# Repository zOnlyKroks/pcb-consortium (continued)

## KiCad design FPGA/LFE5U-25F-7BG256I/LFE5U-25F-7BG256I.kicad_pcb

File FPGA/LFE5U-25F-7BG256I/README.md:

# ECP5 emulation board (LFE5U-25F, caBGA-256)

FPGA board for emulating our custom MCUs and soft cores. Schematic done; PCB placed, fanned out and routed (DRC: 0 unconnected, 0 clearance errors).

## What's on it

| Block | Part | Notes |
|---|---|---|
| FPGA | LFE5U-25F-6BG256C (C1521614) | 24k LUT, 56 DSP, 1 Mbit BRAM. Same footprint and pinout as the -7BG256I placed in the symbol. All banks run at 3.3 V. |
| Config | W25Q32JVSSIQ, 4 MB QSPI | Master SPI boot (CFG = 010). The rest of the flash is free for user data. Buttons for PROGRAMN and a DONE LED. |
| USB | USB-C + CH347F | JTAG to the ECP5 (`openFPGALoader -c ch347`). UART0 + SPI go to bank 7 for the emulated core. Board power comes from USB (1.1 A PTC). |
| RAM | W9812G6KH-6, 16 MB SDR, x16 | 166 MHz. The footprint also fits the 32 MB W9825G6KH; route spare ball M15 to pin 36 (A12) for that. |
| Clock | 25 MHz oscillator on P6 | P6 is the PLL input LLC_GPLL0T_IN. |
| Video | 12-bit VGA (4-4-4 resistor DAC) + HDMI connector | HDMI carries DVI as LVCMOS33D pairs, plus DDC and HPD. |
| Audio | 3.5 mm line out | PWM / sigma-delta through an RC filter. |
| User I/O | 8 LEDs, 8 DIP switches, 4 buttons, 4-digit 7-segment, microSD | |
| Expansion | 4x PMOD (A/B on bank 0, C/D on bank 2) | Also a 40-pin header with 34 GPIO, +5 V, +3.3 V and GND. |
| Power | 2x SY8089 buck (3.3 V, 1.1 V), AP2112K-2.5 LDO (VCCAUX) | |

## Files

- `LFE5U-25F-7BG256I.kicad_sch` is the root sheet. It holds the FPGA units as placed in KiCad, moved right by 63.5 mm so they sit inside the A3 frame. The sub-sheets are power, config, usb_jtag, sdram, video_audio and user_io.
- `constraints/LFE5U-25F-7BG256I.lpf` holds the pin constraints for nextpnr-ecp5 / Diamond: 180 ports, with PULLMODE set for the switches, buttons and SD. Build with `nextpnr-ecp5 --25k --package CABGA256 --speed 6`.
- `tools/design.py` assigns every ball to a net. It is the single source for the schematic labels, the LPF and the netlist check.
- `tools/gen_sch.py` generates every sheet. Re-run it after editing `design.py`. Before re-running, diff `.history` for edits made in KiCad.
- `tools/check_netlist.py` exports the netlist and checks it against `design.py` plus the local nets. It still expects the old references J503/J601 for the audio jack and microSD, which are now CN1/Card1.
- `tools/place_pcb.py` places the PCB, then `tools/fanout_pcb.py` does the BGA and plane fan-out.
- `tools/route_prep.py`, `route_finish.py`, `route_cleanup.py` and `route_leftovers.py` do the routing (see Routing below).
- `tools/build_lib.py` builds `libs/fpga_board.kicad_sym` (SY8089, CH347F).

## PCB

The board is 100 x 100 mm, 6 layers, 1.6 mm thick:

| Layer | Use |
|---|---|
| F.Cu | signals |
| In1 | GND |
| In2 | signals |
| In3 | signals |
| In4 | +3V3, with a +1V1 island under the BGA |
| B.Cu | signals |

It started out as 4 layers. Freerouting stalled there at about 60 unrouted connections on two signal layers, so the board went to 6 layers. The stackup in the board file is JLC's 1.6 mm 6-layer build: 2313 prepreg on the outsides, 0.565 mm cores, and 2116 prepreg in the middle. The values are nominal, because the board is ordered without impedance control. In2 and In3 sit only about 0.13 mm apart, so long parallel runs between them should be avoided.

All parts are on the top side. `tools/place_pcb.py` does the placement: it only moves footprints and sets up the layers, rules and net classes. `tools/fanout_pcb.py` then does the BGA and plane fan-out, and the routing tools do the rest (see below). The edges follow the FPGA banks:

| Edge | What's there | Bank |
|---|---|---|
| Top | PMOD A, PMOD B | 0 |
| Top | HDMI, VGA | 1 |
| Right | microSD, audio, PMOD C/D, with the SDRAM just inside | 2 / 3 |
| Left | USB-C, GPIO header, with power and the CH347 next to the USB | 7 / 6 |
| Bottom | 7-segment, LEDs, DIP switches, buttons; flash and config sit under the BGA | 6 / 8 |

The middle of each BGA side is kept free for fan-out, and the FPGA decoupling sits in the four corners.

### Fan-out

`tools/fanout_pcb.py` escapes all 197 used balls. Each escape ends 1.6 mm outside the outer ball row, so routing starts outside the BGA.

| Balls | Escape |
|---|---|
| Ring 0 (outer row) | F.Cu, straight out |
| Ring 1 | F.Cu, through the channel between two ring-0 balls |
| Ring 2, where a ring-0 channel is still free (8 balls) | F.Cu, straight out, no via |
| Remaining rings 2-5 (94 balls) | Dog-bone via, then a 0.1 mm B.Cu track. A small maze router picks each via's interstitial together with its path. |
| GND, +3V3, +1V1 | Dog-bone via to the plane. F7 and H7 (+3V3 deep in the core) link to their neighbour on F.Cu. |

Why the maze router: straight lanes jam. The ring-2 vias form a wall that passes one track per gap, and between two walls there is room for only one sideways track.

The In4 +1V1 island is shaped around the core. It covers the core square, then runs up an arm through the middle of the top side (no vias in that interstitial column), then along a bar above the BGA. The bar carries all six 100 nF +1V1 caps and C220 from the regulator. For that, C224/C225 swapped places with C242/C243.

The inner planes use 0.1 mm clearance and 0.1 mm minimum width, so copper still flows between two vias 0.8 mm apart. Without that, the 3.3 V plane and the 1.1 V island broke into pieces.

Every other GND/+3V3/+1V1 SMD pad gets a stub and via into its plane where one fits. All fan-out copper is locked, so Freerouting keeps it. Nine plane pads had no room for a via (the regulator side of +1V1, the J502 GND pins, U301 pin 6). Routing ties them to the nearest via of their net. Re-running the script strips the fan-out and redoes it. It refuses to run once there are unlocked (routed) tracks.

Vias must stay out of the In4 arm above the BGA (x 42.4-45.6 mm, y 27-32 mm from the board corner). It is the only feed into the 1.1 V core. A no-via rule area named "+1V1 arm" enforces this, both in DRC and in the Freerouting DSN.

### Routing

1. `tools/route_prep.py` writes `route/LFE5U-25F-7BG256I.dsn`. It takes the plane nets out of the job: Freerouting doesn't treat inner planes as connections, so their fixed copper becomes a netless obstacle. The nine via-less plane pads are routed as small `<net>__<n>` nets to the nearest via of their net. The router's via types are named from the layer count (`Via[0-5]_...` on 6 layers). Earlier the 4-layer names were left in, and Freerouting then could hardly place any vias.
2. Freerouting 2.4.1 from the KiCad plugin, headless:
   `java -Djava.awt.headless=true -jar freerouting-2.4.1.jar -de LFE5U-25F-7BG256I.dsn -do LFE5U-25F-7BG256I.ses -mp 100 -mt 8 --gui.enabled=false --router.job_timeout="01:30:00"`
   It stopped on its own after 28 passes (20 min) with 8 connections open. `route/watch.ps1` shows its progress.
3. `tools/route_finish.py` imports the session, and `tools/route_cleanup.py` strips the copper that leads nowhere. With In2/In3 free, Freerouting mostly left each BGA via on an inner layer, so most 0.1 mm B.Cu escapes ended up as dead ends. Cleanup uses KiCad's DRC to decide what dangles. It trims a track back to a junction rather than deleting it, and it undoes any round that would open a connection.
4. `tools/route_leftovers.py` routes what is still open. It is a 0.05 mm grid router on the four signal layers with rip-up and reroute: other nets' unlocked routing is a soft obstacle, and whatever it crosses gets rerouted. Fan-out, pads and plane copper are hard obstacles. Afterwards it bridges near misses that the grid saw as joined. It routed the last 6 (the HDMI pairs, HDMI_SCL, CH_RXD, GPIO32, PMODD6) after moving a few HDMI/VGA/PMOD-B neighbours.

What DRC still reports is cosmetic: 10 dead-end stubs of 0.02-0.5 mm and 5 vias that join two tracks on one layer, all around the top edge of the BGA. Silk-to-edge and Card1's courtyard were there before routing.

The HDMI pairs are not length-matched or coupled. That's fine at DVI 640x480 (25 MHz pixel clock); higher modes need them redone by hand.

## Notes for layout

- ERC: the remaining warnings come from the LCSC FPGA symbol, whose pins are all "unspecified". The "pin not driven" errors have the same cause: KiCad does not treat an unspecified pin as a driver. Setting the bank pins to bidirectional in the LCSC symbol would clear both.
- microSD (Card1) and audio (CN1) now use the LCSC footprints. The library copies are fixed: the locating pegs are NPTH and the microSD courtyard is a plain rectangle. Run *Update Footprints from Library* on Card1 to pull the courtyard fix in. The HDMI and VGA footprints are still close stock matches. Swap them for the exact LCSC parts with easyeda2kicad before placement. Do the same for the CH347F QFN-28 exposed-pad size.
- Vias come in two sizes:
  - **BGA: 0.2/0.45 mm** (0.125 mm ring). JLC only charges extra for a 0.2 mm hole when the pad is under 0.45 mm. JLC's via rule is a pad at least 0.1 mm larger than the hole, so the ring only needs 0.05 mm.
  - **Cap fan-out: 0.3/0.7 mm**, falling back to 0.3/0.6 mm.
- Inside the package everything runs at 0.1 mm: tracks and gaps on B.Cu, the Power and TMDS net-class clearance, and the plane clearance and minimum width. JLC's multilayer standard is 0.09 mm.
- JLCDFM marks the 0.1 mm tracks, the via rings and the audio jack's 0.5 mm slots as "Danger". It is grading against the 2-layer limits. JLC's multilayer limits are 0.09 mm track/space and 0.35 mm plated slots.
- The fan-out script turns on "subtract soldermask from silkscreen", so the gerbers carry no silk on pads or holes.
- LCSC BOM cost on 2026-10-18 at minimum order quantities: $55.36 for one board, $84.71 for two.

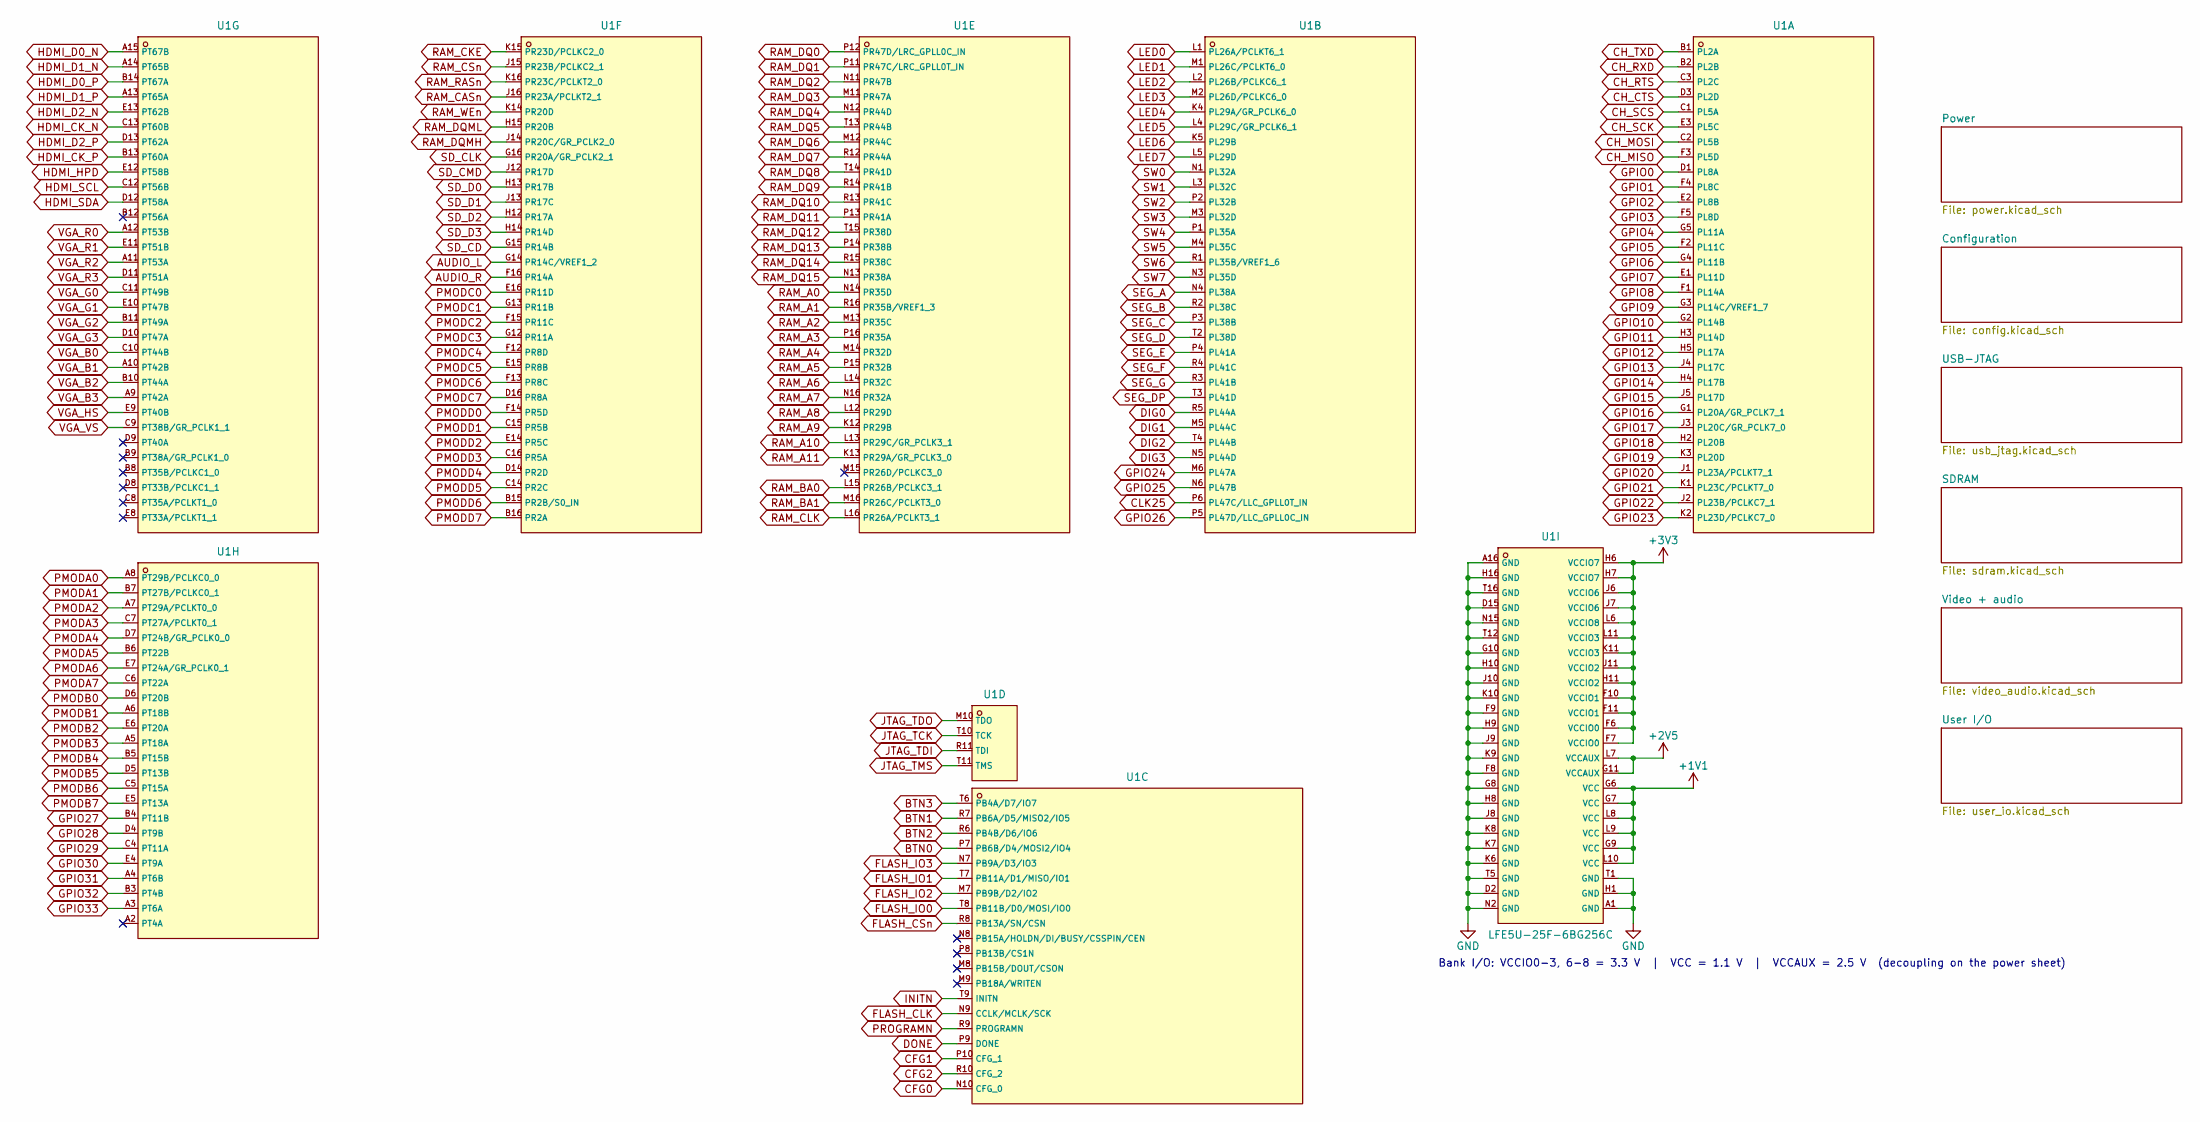
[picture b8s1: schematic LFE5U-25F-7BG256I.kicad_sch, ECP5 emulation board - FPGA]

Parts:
U1: LFE5U-25F-6BG256C; C1550762_CABGA-256_L14_0-W14_0-R16-C16-P0_80-TL; LCSC C1521614

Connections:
+1V1: U1.G6 (VCC), U1.G7 (VCC), U1.G9 (VCC), U1.L8 (VCC), U1.L9 (VCC), U1.L10 (VCC); also elsewhere on the board
+2V5: U1.G11 (VCCAUX), U1.L7 (VCCAUX); also elsewhere on the board
+3V3: U1.F6 (VCCIO0), U1.F7 (VCCIO0), U1.F10 (VCCIO1), U1.F11 (VCCIO1), U1.H6 (VCCIO7), U1.H7 (VCCIO7), U1.H11 (VCCIO2), U1.J6 (VCCIO6), U1.J7 (VCCIO6), U1.J11 (VCCIO2), U1.K11 (VCCIO3), U1.L6 (VCCIO8), U1.L11 (VCCIO3); also elsewhere on the board
AUDIO_L: U1.G14 (PR14C/VREF1_2); also elsewhere on the board
AUDIO_R: U1.F16 (PR14A); also elsewhere on the board
BTN0: U1.P7 (PB6B/D4/MOSI2/IO4); also elsewhere on the board
BTN1: U1.R7 (PB6A/D5/MISO2/IO5); also elsewhere on the board
BTN2: U1.R6 (PB4B/D6/IO6); also elsewhere on the board
BTN3: U1.T6 (PB4A/D7/IO7); also elsewhere on the board
CFG0: U1.N10 (CFG_0); also elsewhere on the board
CFG1: U1.P10 (CFG_1); also elsewhere on the board
CFG2: U1.R10 (CFG_2); also elsewhere on the board
CH_CTS: U1.D3 (PL2D); also elsewhere on the board
CH_MISO: U1.F3 (PL5D); also elsewhere on the board
CH_MOSI: U1.C2 (PL5B); also elsewhere on the board
CH_RTS: U1.C3 (PL2C); also elsewhere on the board
CH_RXD: U1.B2 (PL2B); also elsewhere on the board
CH_SCK: U1.E3 (PL5C); also elsewhere on the board
CH_SCS: U1.C1 (PL5A); also elsewhere on the board
CH_TXD: U1.B1 (PL2A); also elsewhere on the board
CLK25: U1.P6 (PL47C/LLC_GPLL0T_IN); also elsewhere on the board
DIG0: U1.R5 (PL44A); also elsewhere on the board
DIG1: U1.M5 (PL44C); also elsewhere on the board
DIG2: U1.T4 (PL44B); also elsewhere on the board
DIG3: U1.N5 (PL44D); also elsewhere on the board
DONE: U1.P9 (DONE); also elsewhere on the board
FLASH_CLK: U1.N9 (CCLK/MCLK/SCK); also elsewhere on the board
FLASH_CSn: U1.R8 (PB13A/SN/CSN); also elsewhere on the board
FLASH_IO0: U1.T8 (PB11B/D0/MOSI/IO0); also elsewhere on the board
FLASH_IO1: U1.T7 (PB11A/D1/MISO/IO1); also elsewhere on the board
FLASH_IO2: U1.M7 (PB9B/D2/IO2); also elsewhere on the board
FLASH_IO3: U1.N7 (PB9A/D3/IO3); also elsewhere on the board
GND: U1.A1 (GND), U1.A16 (GND), U1.D2 (GND), U1.D15 (GND), U1.F8 (GND), U1.F9 (GND), U1.G8 (GND), U1.G10 (GND), U1.H1 (GND), U1.H8 (GND), U1.H9 (GND), U1.H10 (GND), U1.H16 (GND), U1.J8 (GND), U1.J9 (GND), U1.J10 (GND), U1.K6 (GND), U1.K7 (GND), U1.K8 (GND), U1.K9 (GND), U1.K10 (GND), U1.N2 (GND), U1.N15 (GND), U1.T1 (GND), U1.T5 (GND), U1.T12 (GND), U1.T16 (GND); also elsewhere on the board
GPIO0: U1.D1 (PL8A); also elsewhere on the board
GPIO1: U1.F4 (PL8C); also elsewhere on the board
GPIO2: U1.E2 (PL8B); also elsewhere on the board
GPIO3: U1.F5 (PL8D); also elsewhere on the board
GPIO4: U1.G5 (PL11A); also elsewhere on the board
GPIO5: U1.F2 (PL11C); also elsewhere on the board
GPIO6: U1.G4 (PL11B); also elsewhere on the board
GPIO7: U1.E1 (PL11D); also elsewhere on the board
GPIO8: U1.F1 (PL14A); also elsewhere on the board
GPIO9: U1.G3 (PL14C/VREF1_7); also elsewhere on the board
GPIO10: U1.G2 (PL14B); also elsewhere on the board
GPIO11: U1.H3 (PL14D); also elsewhere on the board
GPIO12: U1.H5 (PL17A); also elsewhere on the board
GPIO13: U1.J4 (PL17C); also elsewhere on the board
GPIO14: U1.H4 (PL17B); also elsewhere on the board
GPIO15: U1.J5 (PL17D); also elsewhere on the board
GPIO16: U1.G1 (PL20A/GR_PCLK7_1); also elsewhere on the board
GPIO17: U1.J3 (PL20C/GR_PCLK7_0); also elsewhere on the board
GPIO18: U1.H2 (PL20B); also elsewhere on the board
GPIO19: U1.K3 (PL20D); also elsewhere on the board
GPIO20: U1.J1 (PL23A/PCLKT7_1); also elsewhere on the board
GPIO21: U1.K1 (PL23C/PCLKT7_0); also elsewhere on the board
GPIO22: U1.J2 (PL23B/PCLKC7_1); also elsewhere on the board
GPIO23: U1.K2 (PL23D/PCLKC7_0); also elsewhere on the board
GPIO24: U1.M6 (PL47A); also elsewhere on the board
GPIO25: U1.N6 (PL47B); also elsewhere on the board
GPIO26: U1.P5 (PL47D/LLC_GPLL0C_IN); also elsewhere on the board
GPIO27: U1.B4 (PT11B); also elsewhere on the board
GPIO28: U1.D4 (PT9B); also elsewhere on the board
GPIO29: U1.C4 (PT11A); also elsewhere on the board
GPIO30: U1.E4 (PT9A); also elsewhere on the board
GPIO31: U1.A4 (PT6B); also elsewhere on the board
GPIO32: U1.B3 (PT4B); also elsewhere on the board
GPIO33: U1.A3 (PT6A); also elsewhere on the board
HDMI_CK_N: U1.C13 (PT60B); also elsewhere on the board
HDMI_CK_P: U1.B13 (PT60A); also elsewhere on the board
HDMI_D0_N: U1.A15 (PT67B); also elsewhere on the board
HDMI_D0_P: U1.B14 (PT67A); also elsewhere on the board
HDMI_D1_N: U1.A14 (PT65B); also elsewhere on the board
HDMI_D1_P: U1.A13 (PT65A); also elsewhere on the board
HDMI_D2_N: U1.E13 (PT62B); also elsewhere on the board
HDMI_D2_P: U1.D13 (PT62A); also elsewhere on the board
HDMI_HPD: U1.E12 (PT58B); also elsewhere on the board
HDMI_SCL: U1.C12 (PT56B); also elsewhere on the board
HDMI_SDA: U1.D12 (PT58A); also elsewhere on the board
INITN: U1.T9 (INITN); also elsewhere on the board
JTAG_TCK: U1.T10 (TCK); also elsewhere on the board
JTAG_TDI: U1.R11 (TDI); also elsewhere on the board
JTAG_TDO: U1.M10 (TDO); also elsewhere on the board
JTAG_TMS: U1.T11 (TMS); also elsewhere on the board
LED0: U1.L1 (PL26A/PCLKT6_1); also elsewhere on the board
LED1: U1.M1 (PL26C/PCLKT6_0); also elsewhere on the board
LED2: U1.L2 (PL26B/PCLKC6_1); also elsewhere on the board
LED3: U1.M2 (PL26D/PCLKC6_0); also elsewhere on the board
LED4: U1.K4 (PL29A/GR_PCLK6_0); also elsewhere on the board
LED5: U1.L4 (PL29C/GR_PCLK6_1); also elsewhere on the board
LED6: U1.K5 (PL29B); also elsewhere on the board
LED7: U1.L5 (PL29D); also elsewhere on the board
PMODA0: U1.A8 (PT29B/PCLKC0_0); also elsewhere on the board
PMODA1: U1.B7 (PT27B/PCLKC0_1); also elsewhere on the board
PMODA2: U1.A7 (PT29A/PCLKT0_0); also elsewhere on the board
PMODA3: U1.C7 (PT27A/PCLKT0_1); also elsewhere on the board
PMODA4: U1.D7 (PT24B/GR_PCLK0_0); also elsewhere on the board
PMODA5: U1.B6 (PT22B); also elsewhere on the board
PMODA6: U1.E7 (PT24A/GR_PCLK0_1); also elsewhere on the board
PMODA7: U1.C6 (PT22A); also elsewhere on the board
PMODB0: U1.D6 (PT20B); also elsewhere on the board
PMODB1: U1.A6 (PT18B); also elsewhere on the board
PMODB2: U1.E6 (PT20A); also elsewhere on the board
PMODB3: U1.A5 (PT18A); also elsewhere on the board
PMODB4: U1.B5 (PT15B); also elsewhere on the board
PMODB5: U1.D5 (PT13B); also elsewhere on the board
PMODB6: U1.C5 (PT15A); also elsewhere on the board
PMODB7: U1.E5 (PT13A); also elsewhere on the board
PMODC0: U1.E16 (PR11D); also elsewhere on the board
PMODC1: U1.G13 (PR11B); also elsewhere on the board
PMODC2: U1.F15 (PR11C); also elsewhere on the board
PMODC3: U1.G12 (PR11A); also elsewhere on the board
PMODC4: U1.F12 (PR8D); also elsewhere on the board
PMODC5: U1.E15 (PR8B); also elsewhere on the board
PMODC6: U1.F13 (PR8C); also elsewhere on the board
PMODC7: U1.D16 (PR8A); also elsewhere on the board
PMODD0: U1.F14 (PR5D); also elsewhere on the board
PMODD1: U1.C15 (PR5B); also elsewhere on the board
PMODD2: U1.E14 (PR5C); also elsewhere on the board
PMODD3: U1.C16 (PR5A); also elsewhere on the board
PMODD4: U1.D14 (PR2D); also elsewhere on the board
PMODD5: U1.C14 (PR2C); also elsewhere on the board
PMODD6: U1.B15 (PR2B/S0_IN); also elsewhere on the board
PMODD7: U1.B16 (PR2A); also elsewhere on the board
PROGRAMN: U1.R9 (PROGRAMN); also elsewhere on the board
RAM_A0: U1.N14 (PR35D); also elsewhere on the board
RAM_A1: U1.R16 (PR35B/VREF1_3); also elsewhere on the board
RAM_A2: U1.M13 (PR35C); also elsewhere on the board
RAM_A3: U1.P16 (PR35A); also elsewhere on the board
RAM_A4: U1.M14 (PR32D); also elsewhere on the board
RAM_A5: U1.P15 (PR32B); also elsewhere on the board
RAM_A6: U1.L14 (PR32C); also elsewhere on the board
RAM_A7: U1.N16 (PR32A); also elsewhere on the board
RAM_A8: U1.L12 (PR29D); also elsewhere on the board
RAM_A9: U1.K12 (PR29B); also elsewhere on the board
RAM_A10: U1.L13 (PR29C/GR_PCLK3_1); also elsewhere on the board
RAM_A11: U1.K13 (PR29A/GR_PCLK3_0); also elsewhere on the board
RAM_BA0: U1.L15 (PR26B/PCLKC3_1); also elsewhere on the board
RAM_BA1: U1.M16 (PR26C/PCLKT3_0); also elsewhere on the board
RAM_CASn: U1.J16 (PR23A/PCLKT2_1); also elsewhere on the board
RAM_CKE: U1.K15 (PR23D/PCLKC2_0); also elsewhere on the board
RAM_CLK: U1.L16 (PR26A/PCLKT3_1); also elsewhere on the board
RAM_CSn: U1.J15 (PR23B/PCLKC2_1); also elsewhere on the board
RAM_DQ0: U1.P12 (PR47D/LRC_GPLL0C_IN); also elsewhere on the board
RAM_DQ1: U1.P11 (PR47C/LRC_GPLL0T_IN); also elsewhere on the board
RAM_DQ2: U1.N11 (PR47B); also elsewhere on the board
RAM_DQ3: U1.M11 (PR47A); also elsewhere on the board
RAM_DQ4: U1.N12 (PR44D); also elsewhere on the board
RAM_DQ5: U1.T13 (PR44B); also elsewhere on the board
RAM_DQ6: U1.M12 (PR44C); also elsewhere on the board
RAM_DQ7: U1.R12 (PR44A); also elsewhere on the board
RAM_DQ8: U1.T14 (PR41D); also elsewhere on the board
RAM_DQ9: U1.R14 (PR41B); also elsewhere on the board
RAM_DQ10: U1.R13 (PR41C); also elsewhere on the board
RAM_DQ11: U1.P13 (PR41A); also elsewhere on the board
RAM_DQ12: U1.T15 (PR38D); also elsewhere on the board
RAM_DQ13: U1.P14 (PR38B); also elsewhere on the board
RAM_DQ14: U1.R15 (PR38C); also elsewhere on the board
RAM_DQ15: U1.N13 (PR38A); also elsewhere on the board
RAM_DQMH: U1.J14 (PR20C/GR_PCLK2_0); also elsewhere on the board
RAM_DQML: U1.H15 (PR20B); also elsewhere on the board
RAM_RASn: U1.K16 (PR23C/PCLKT2_0); also elsewhere on the board
RAM_WEn: U1.K14 (PR20D); also elsewhere on the board
SD_CD: U1.G15 (PR14B); also elsewhere on the board
SD_CLK: U1.G16 (PR20A/GR_PCLK2_1); also elsewhere on the board
SD_CMD: U1.J12 (PR17D); also elsewhere on the board
SD_D0: U1.H13 (PR17B); also elsewhere on the board
SD_D1: U1.J13 (PR17C); also elsewhere on the board
SD_D2: U1.H12 (PR17A); also elsewhere on the board
SD_D3: U1.H14 (PR14D); also elsewhere on the board
SEG_A: U1.N4 (PL38A); also elsewhere on the board
SEG_B: U1.R2 (PL38C); also elsewhere on the board
SEG_C: U1.P3 (PL38B); also elsewhere on the board
SEG_D: U1.T2 (PL38D); also elsewhere on the board
SEG_DP: U1.T3 (PL41D); also elsewhere on the board
SEG_E: U1.P4 (PL41A); also elsewhere on the board
SEG_F: U1.R4 (PL41C); also elsewhere on the board
SEG_G: U1.R3 (PL41B); also elsewhere on the board
SW0: U1.N1 (PL32A); also elsewhere on the board
SW1: U1.L3 (PL32C); also elsewhere on the board
SW2: U1.P2 (PL32B); also elsewhere on the board
SW3: U1.M3 (PL32D); also elsewhere on the board
SW4: U1.P1 (PL35A); also elsewhere on the board
SW5: U1.M4 (PL35C); also elsewhere on the board
SW6: U1.R1 (PL35B/VREF1_6); also elsewhere on the board
SW7: U1.N3 (PL35D); also elsewhere on the board
VGA_B0: U1.C10 (PT44B); also elsewhere on the board
VGA_B1: U1.A10 (PT42B); also elsewhere on the board
VGA_B2: U1.B10 (PT44A); also elsewhere on the board
VGA_B3: U1.A9 (PT42A); also elsewhere on the board
VGA_G0: U1.C11 (PT49B); also elsewhere on the board
VGA_G1: U1.E10 (PT47B); also elsewhere on the board
VGA_G2: U1.B11 (PT49A); also elsewhere on the board
VGA_G3: U1.D10 (PT47A); also elsewhere on the board
VGA_HS: U1.E9 (PT40B); also elsewhere on the board
VGA_R0: U1.A12 (PT53B); also elsewhere on the board
VGA_R1: U1.E11 (PT51B); also elsewhere on the board
VGA_R2: U1.A11 (PT53A); also elsewhere on the board
VGA_R3: U1.D11 (PT51A); also elsewhere on the board
VGA_VS: U1.C9 (PT38B/GR_PCLK1_1); also elsewhere on the board

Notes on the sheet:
Bank I/O: VCCIO0-3, 6-8 = 3.3 V | VCC = 1.1 V | VCCAUX = 2.5 V (decoupling on the power sheet)

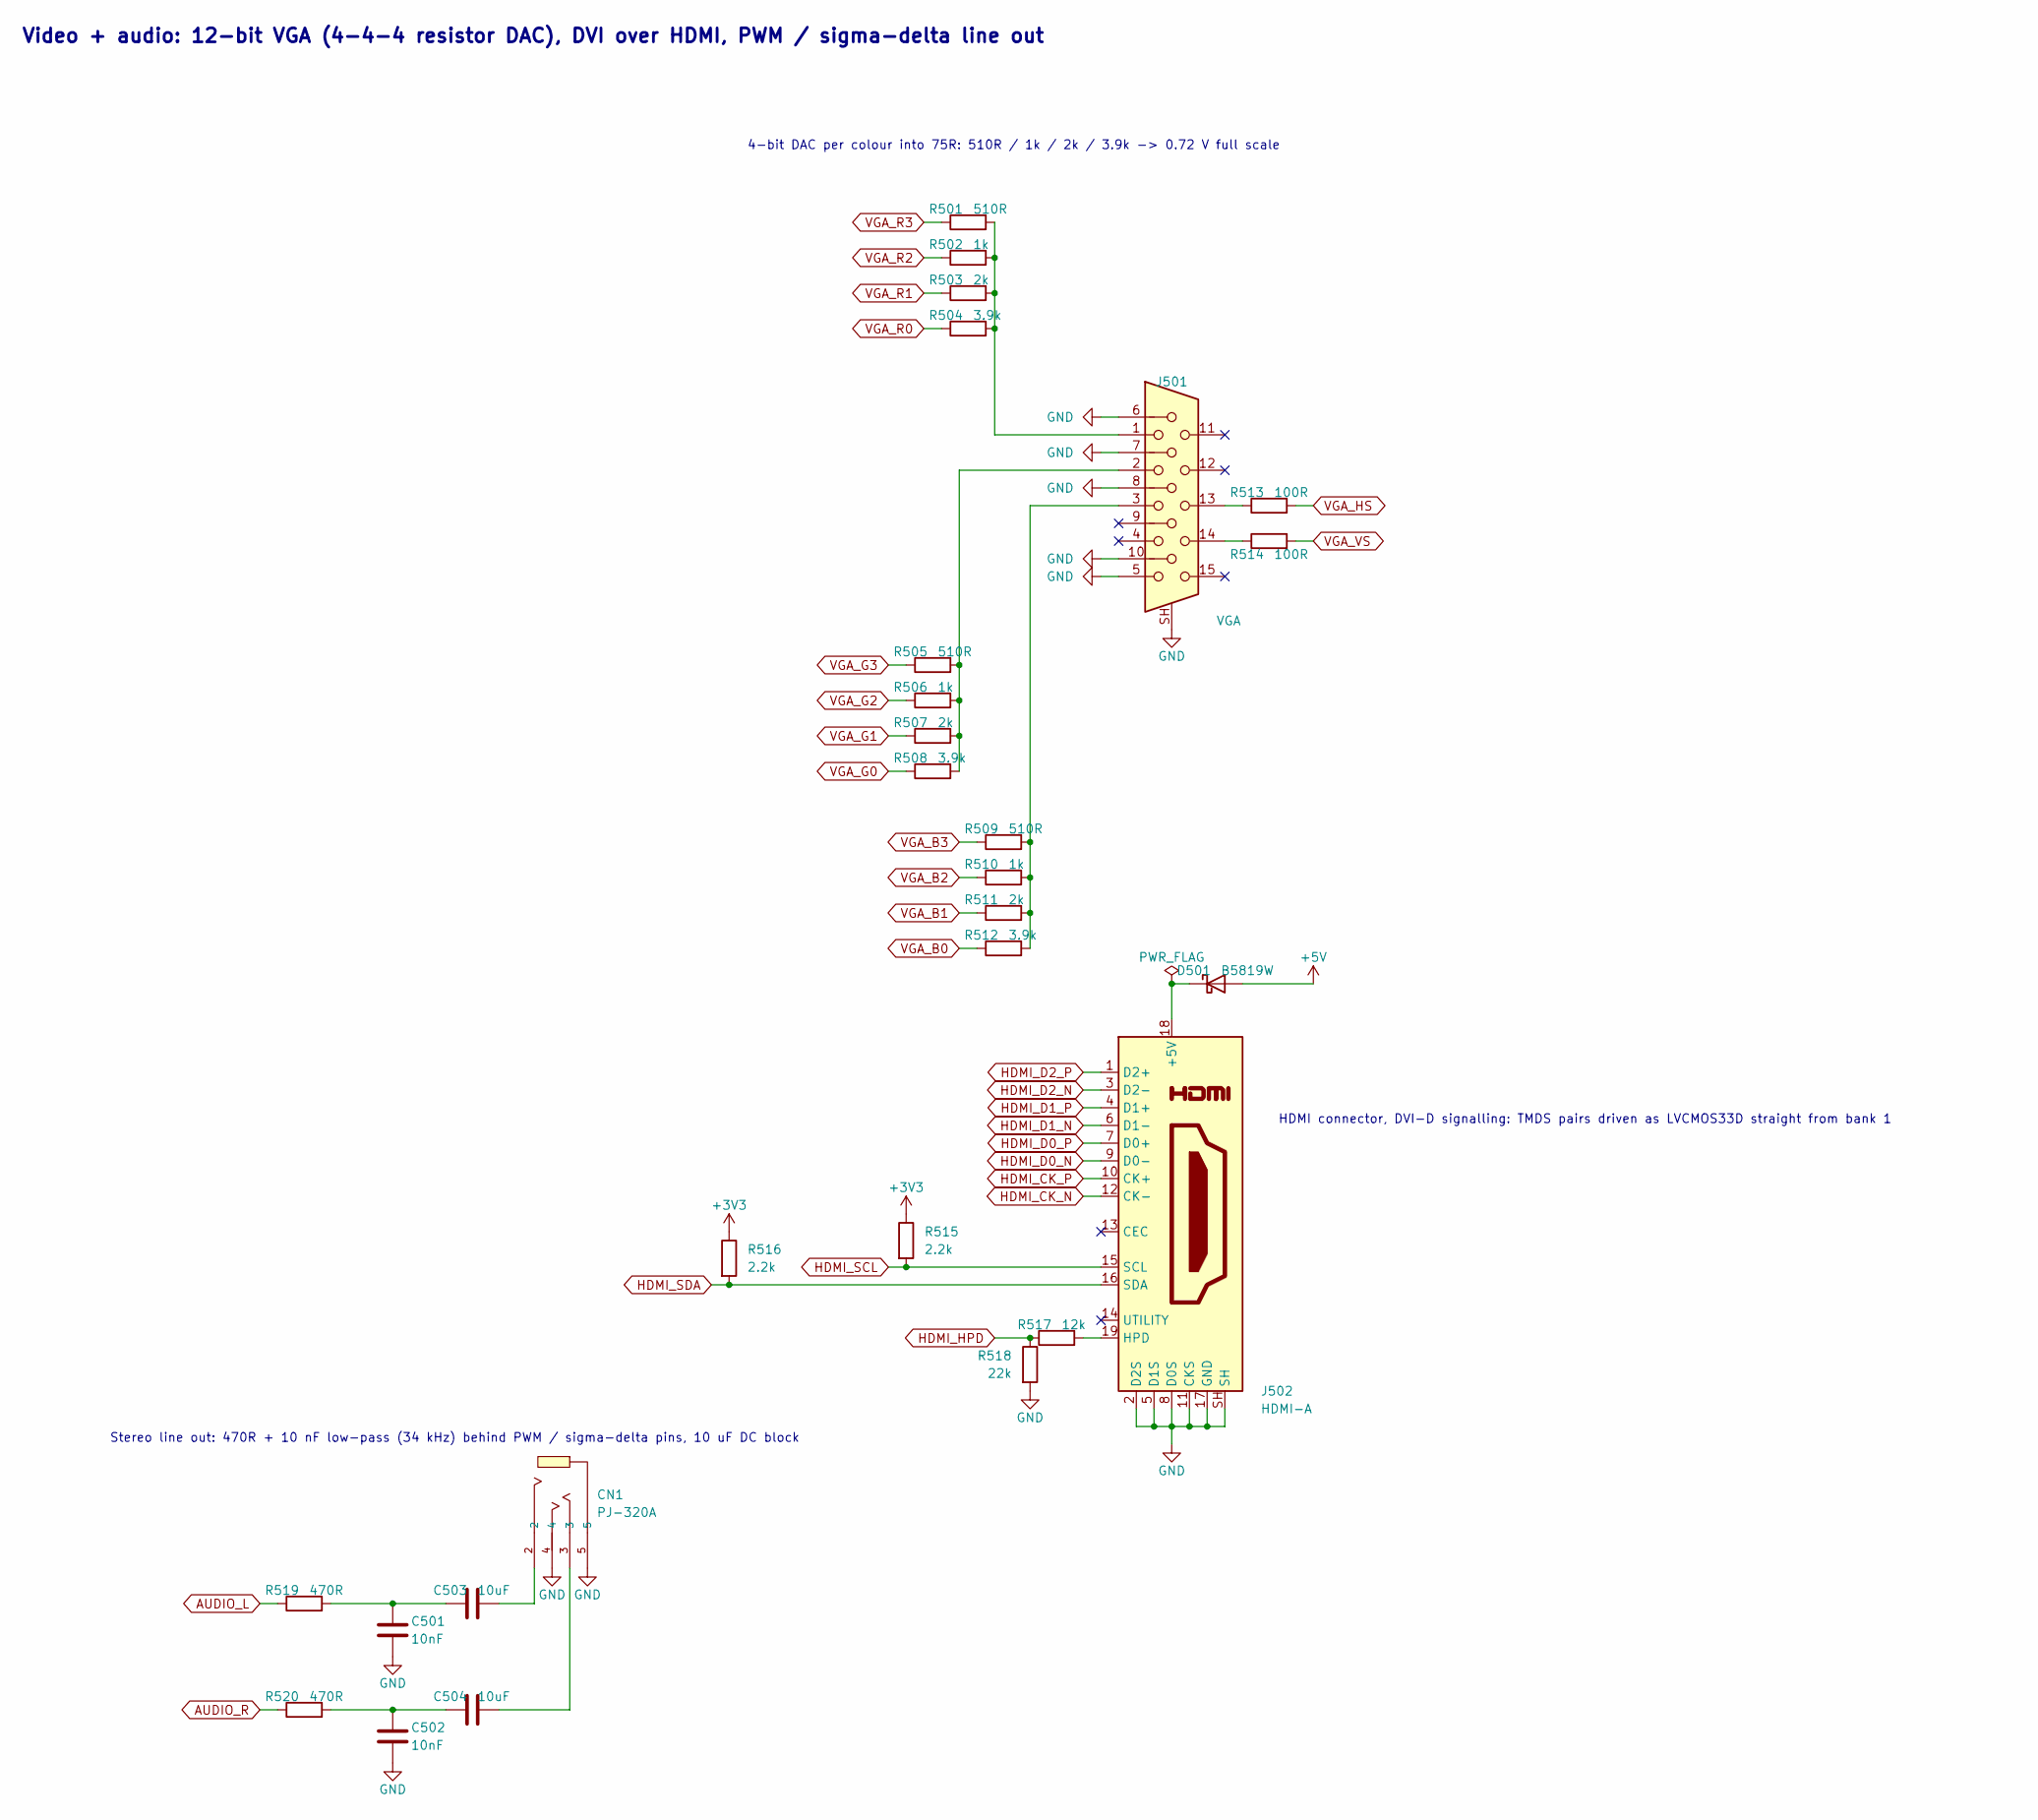
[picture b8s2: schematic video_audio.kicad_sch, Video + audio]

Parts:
C501, C502: 10nF; C_0603_1608Metric; LCSC Part # C1589
C503, C504: 10uF; C_0603_1608Metric; LCSC Part # C19702
CN1: PJ-320A; C2884926_AUDIO-TH_XKB_PJ-320A; LCSC C2884926
D501: B5819W; D_SOD-123; LCSC Part # C64885
J501: VGA; DSUB-15-HD_Socket_Horizontal_P2.29x1.90mm_EdgePinOffset3.03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; MPN D-DMRH15PF-E006; LCSC Part # C379814
J502: HDMI-A; HDMI_A_Molex_208658-1001_Horizontal; MPN HDMI-001 19PCBTP; LCSC Part # C138388
R501, R505, R509: 510R; R_0603_1608Metric; LCSC Part # C23193
R502, R506, R510: 1k; R_0603_1608Metric; LCSC Part # C22548
R503, R507, R511: 2k; R_0603_1608Metric; LCSC Part # C22975
R504, R508, R512: 3.9k; R_0603_1608Metric; LCSC Part # C23018
R513, R514: 100R; R_0603_1608Metric; LCSC Part # C22775
R515, R516: 2.2k; R_0603_1608Metric; LCSC Part # C4190
R517: 12k; R_0603_1608Metric; LCSC Part # C22790
R518: 22k; R_0603_1608Metric; LCSC Part # C31850
R519, R520: 470R; R_0603_1608Metric; LCSC Part # C23179

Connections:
+3V3: R515.1, R516.1; also elsewhere on the board
+5V: D501.2 (A); also elsewhere on the board
AUDIO_L: R519.1; also elsewhere on the board
AUDIO_R: R520.1; also elsewhere on the board
GND: C501.2, C502.2, CN1.4, CN1.5, J501.5, J501.6, J501.7, J501.8, J501.10, J501.SH, J502.2 (D2S), J502.5 (D1S), J502.8 (D0S), J502.11 (CKS), J502.17 (GND), J502.SH, R518.2; also elsewhere on the board
HDMI_CK_N: J502.12 (CK-); also elsewhere on the board
HDMI_CK_P: J502.10 (CK+); also elsewhere on the board
HDMI_D0_N: J502.9 (D0-); also elsewhere on the board
HDMI_D0_P: J502.7 (D0+); also elsewhere on the board
HDMI_D1_N: J502.6 (D1-); also elsewhere on the board
HDMI_D1_P: J502.4 (D1+); also elsewhere on the board
HDMI_D2_N: J502.3 (D2-); also elsewhere on the board
HDMI_D2_P: J502.1 (D2+); also elsewhere on the board
HDMI_HPD: R517.1, R518.1; also elsewhere on the board
HDMI_SCL: J502.15 (SCL), R515.2; also elsewhere on the board
HDMI_SDA: J502.16 (SDA), R516.2; also elsewhere on the board
unnamed: C501.1, C503.1, R519.2
unnamed: C502.1, C504.1, R520.2
unnamed: C503.2, CN1.2
unnamed: C504.2, CN1.3
unnamed: D501.1 (K), J502.18 (+5V)
unnamed: J501.1, R501.2, R502.2, R503.2, R504.2
unnamed: J501.2, R505.2, R506.2, R507.2, R508.2
unnamed: J501.3, R509.2, R510.2, R511.2, R512.2
unnamed: J501.13, R513.1
unnamed: J501.14, R514.1
unnamed: J502.19 (HPD), R517.2
VGA_B0: R512.1; also elsewhere on the board
VGA_B1: R511.1; also elsewhere on the board
VGA_B2: R510.1; also elsewhere on the board
VGA_B3: R509.1; also elsewhere on the board
VGA_G0: R508.1; also elsewhere on the board
VGA_G1: R507.1; also elsewhere on the board
VGA_G2: R506.1; also elsewhere on the board
VGA_G3: R505.1; also elsewhere on the board
VGA_HS: R513.2; also elsewhere on the board
VGA_R0: R504.1; also elsewhere on the board
VGA_R1: R503.1; also elsewhere on the board
VGA_R2: R502.1; also elsewhere on the board
VGA_R3: R501.1; also elsewhere on the board
VGA_VS: R514.2; also elsewhere on the board

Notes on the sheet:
Stereo line out: 470R + 10 nF low-pass (34 kHz) behind PWM / sigma-delta pins, 10 uF DC block
4-bit DAC per colour into 75R: 510R / 1k / 2k / 3.9k -> 0.72 V full scale
HDMI connector, DVI-D signalling: TMDS pairs driven as LVCMOS33D straight from bank 1
Video + audio: 12-bit VGA (4-4-4 resistor DAC), DVI over HDMI, PWM / sigma-delta line out

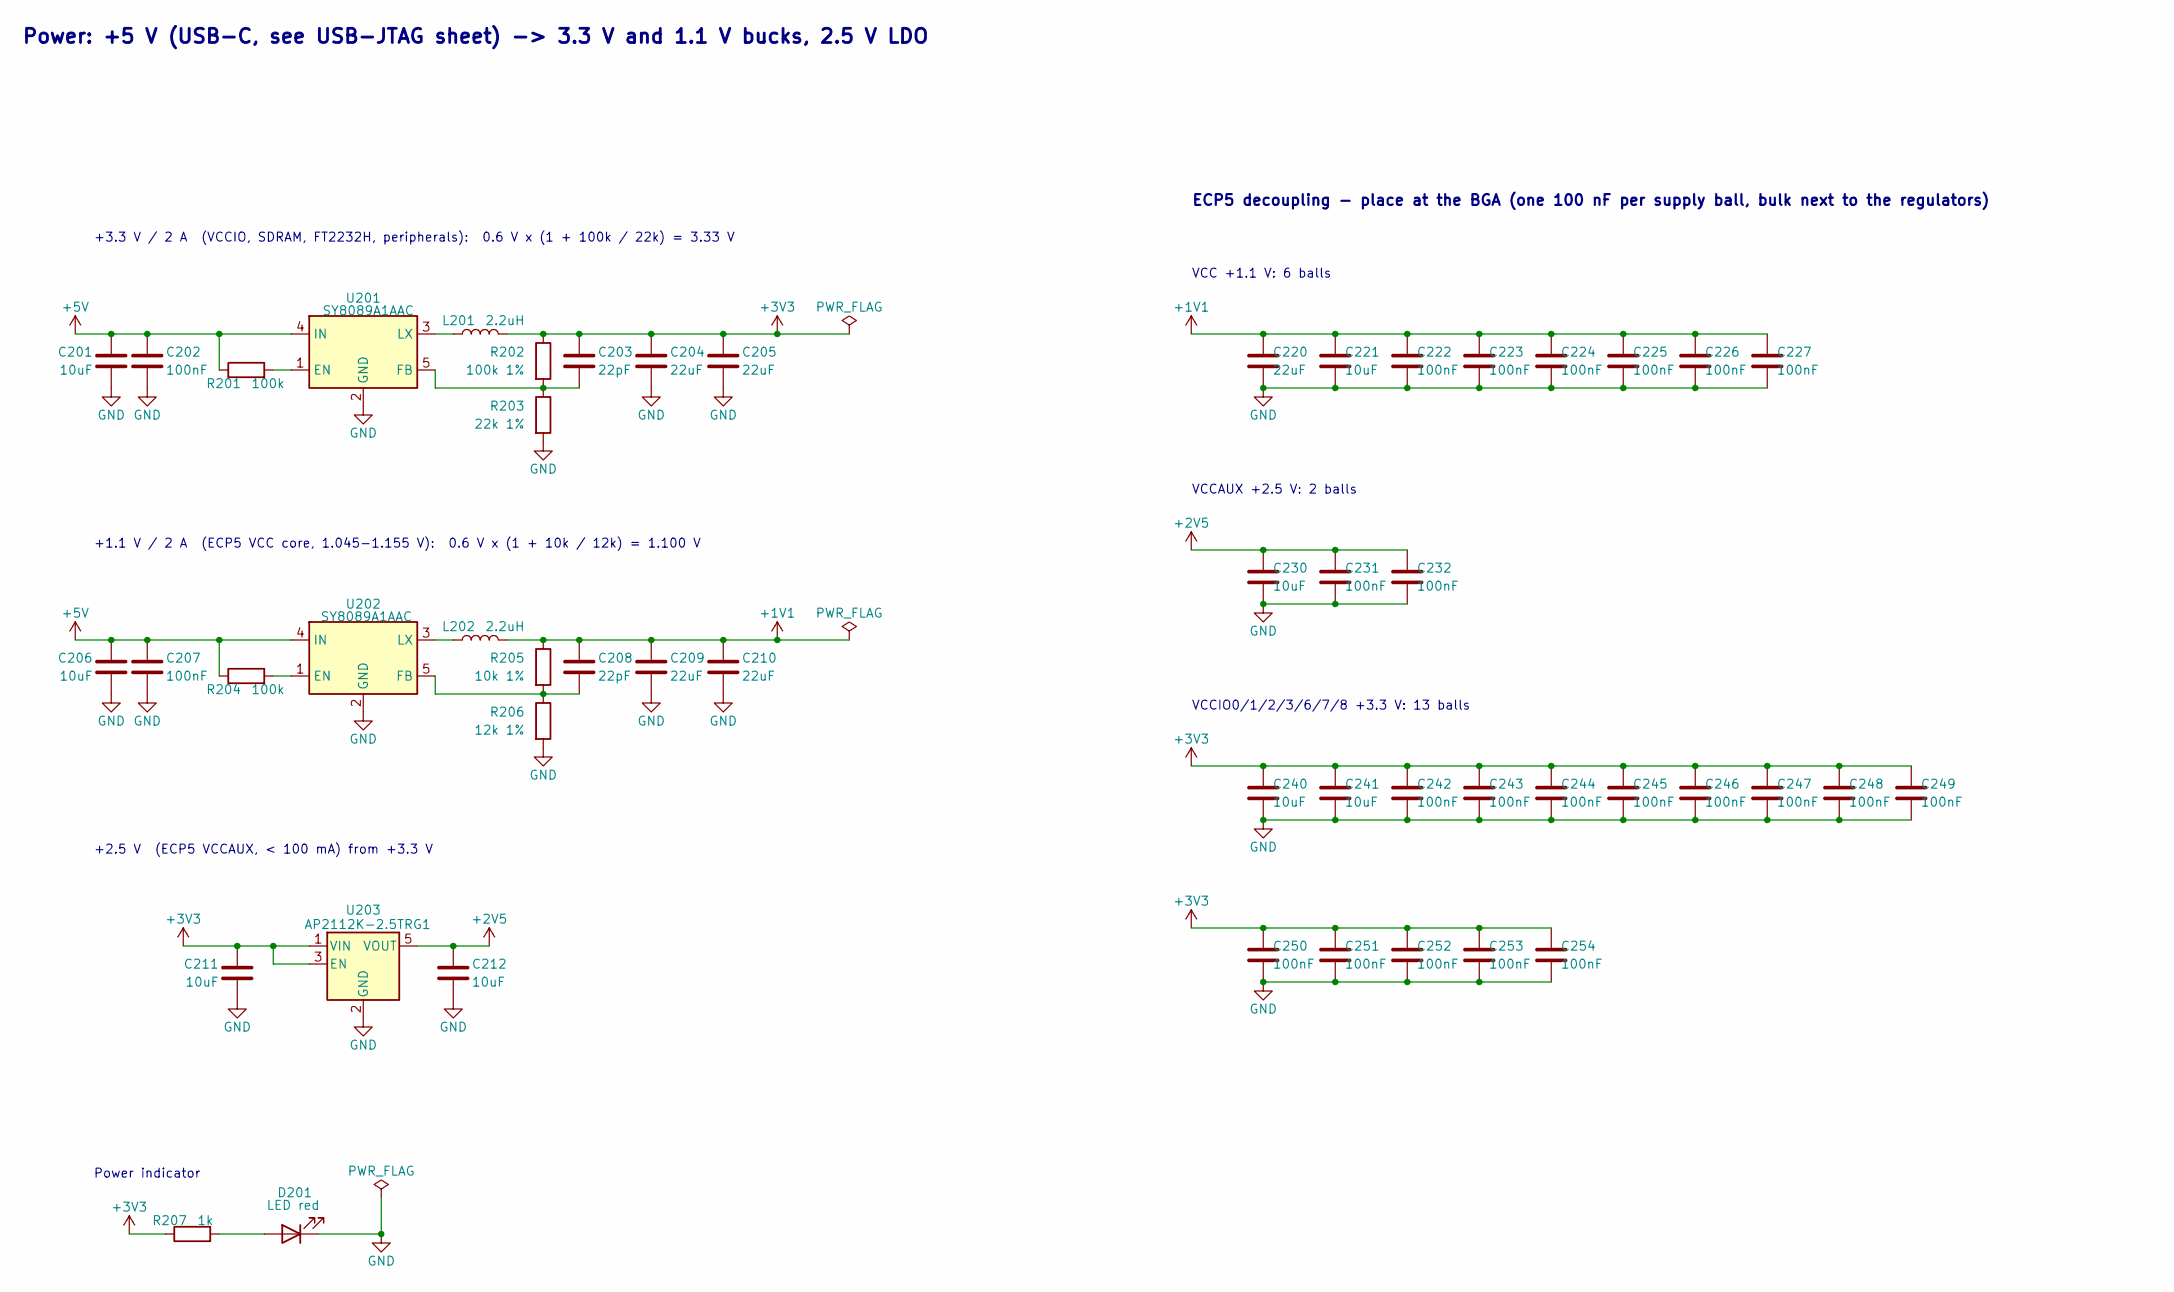
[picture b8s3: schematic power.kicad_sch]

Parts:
C201, C206, C211, C212, C221, C230, C240, C241: 10uF; C_0603_1608Metric; LCSC Part # C19702
C202, C207, C222, C223, C224, C225, C226, C227, C231, C232, C242, C243, C244, C245, C246, C247, C248, C249, C250, C251, C252, C253, C254: 100nF; C_0603_1608Metric; LCSC Part # C14663
C203, C208: 22pF; C_0603_1608Metric; LCSC Part # C1653
C204, C205, C209, C210, C220: 22uF; C_0805_2012Metric; LCSC Part # C380338
D201: LED red; LED_0603_1608Metric; LCSC Part # C2286
L201, L202: 2.2uH; L_Changjiang_FNR4020S; LCSC Part # C167825
R201, R204: 100k; R_0603_1608Metric; LCSC Part # C25803
R202: 100k 1%; R_0603_1608Metric; LCSC Part # C25803
R203: 22k 1%; R_0603_1608Metric; LCSC Part # C31850
R205: 10k 1%; R_0603_1608Metric; LCSC Part # C25804
R206: 12k 1%; R_0603_1608Metric; LCSC Part # C22790
R207: 1k; R_0603_1608Metric; LCSC Part # C22548
U201, U202: SY8089A1AAC; SOT-23-5; LCSC Part # C479074
U203: AP2112K-2.5TRG1; SOT-23-5; LCSC Part # C176945

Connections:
+1V1: C208.1, C209.1, C210.1, C220.1, C221.1, C222.1, C223.1, C224.1, C225.1, C226.1, C227.1, L202.2, R205.1; also elsewhere on the board
+2V5: C212.1, C230.1, C231.1, C232.1, U203.5 (VOUT); also elsewhere on the board
+3V3: C203.1, C204.1, C205.1, C211.1, C240.1, C241.1, C242.1, C243.1, C244.1, C245.1, C246.1, C247.1, C248.1, C249.1, C250.1, C251.1, C252.1, C253.1, C254.1, L201.2, R202.1, R207.1, U203.1 (VIN), U203.3 (EN); also elsewhere on the board
+5V: C201.1, C202.1, C206.1, C207.1, R201.1, R204.1, U201.4 (IN), U202.4 (IN); also elsewhere on the board
GND: C201.2, C202.2, C204.2, C205.2, C206.2, C207.2, C209.2, C210.2, C211.2, C212.2, C220.2, C221.2, C222.2, C223.2, C224.2, C225.2, C226.2, C227.2, C230.2, C231.2, C232.2, C240.2, C241.2, C242.2, C243.2, C244.2, C245.2, C246.2, C247.2, C248.2, C249.2, C250.2, C251.2, C252.2, C253.2, C254.2, D201.1 (K), R203.2, R206.2, U201.2 (GND), U202.2 (GND), U203.2 (GND); also elsewhere on the board
unnamed: D201.2 (A), R207.2
unnamed: R201.2, U201.1 (EN)
unnamed: C203.2, R202.2, R203.1, U201.5 (FB)
unnamed: L201.1, U201.3 (LX)
unnamed: R204.2, U202.1 (EN)
unnamed: C208.2, R205.2, R206.1, U202.5 (FB)
unnamed: L202.1, U202.3 (LX)

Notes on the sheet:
VCCAUX +2.5 V: 2 balls
Power: +5 V (USB-C, see USB-JTAG sheet) -> 3.3 V and 1.1 V bucks, 2.5 V LDO
VCCIO0/1/2/3/6/7/8 +3.3 V: 13 balls
VCC +1.1 V: 6 balls
+1.1 V / 2 A (ECP5 VCC core, 1.045-1.155 V): 0.6 V x (1 + 10k / 12k) = 1.100 V
+3.3 V / 2 A (VCCIO, SDRAM, FT2232H, peripherals): 0.6 V x (1 + 100k / 22k) = 3.33 V
Power indicator
+2.5 V (ECP5 VCCAUX, < 100 mA) from +3.3 V
ECP5 decoupling - place at the BGA (one 100 nF per supply ball, bulk next to the regulators)
